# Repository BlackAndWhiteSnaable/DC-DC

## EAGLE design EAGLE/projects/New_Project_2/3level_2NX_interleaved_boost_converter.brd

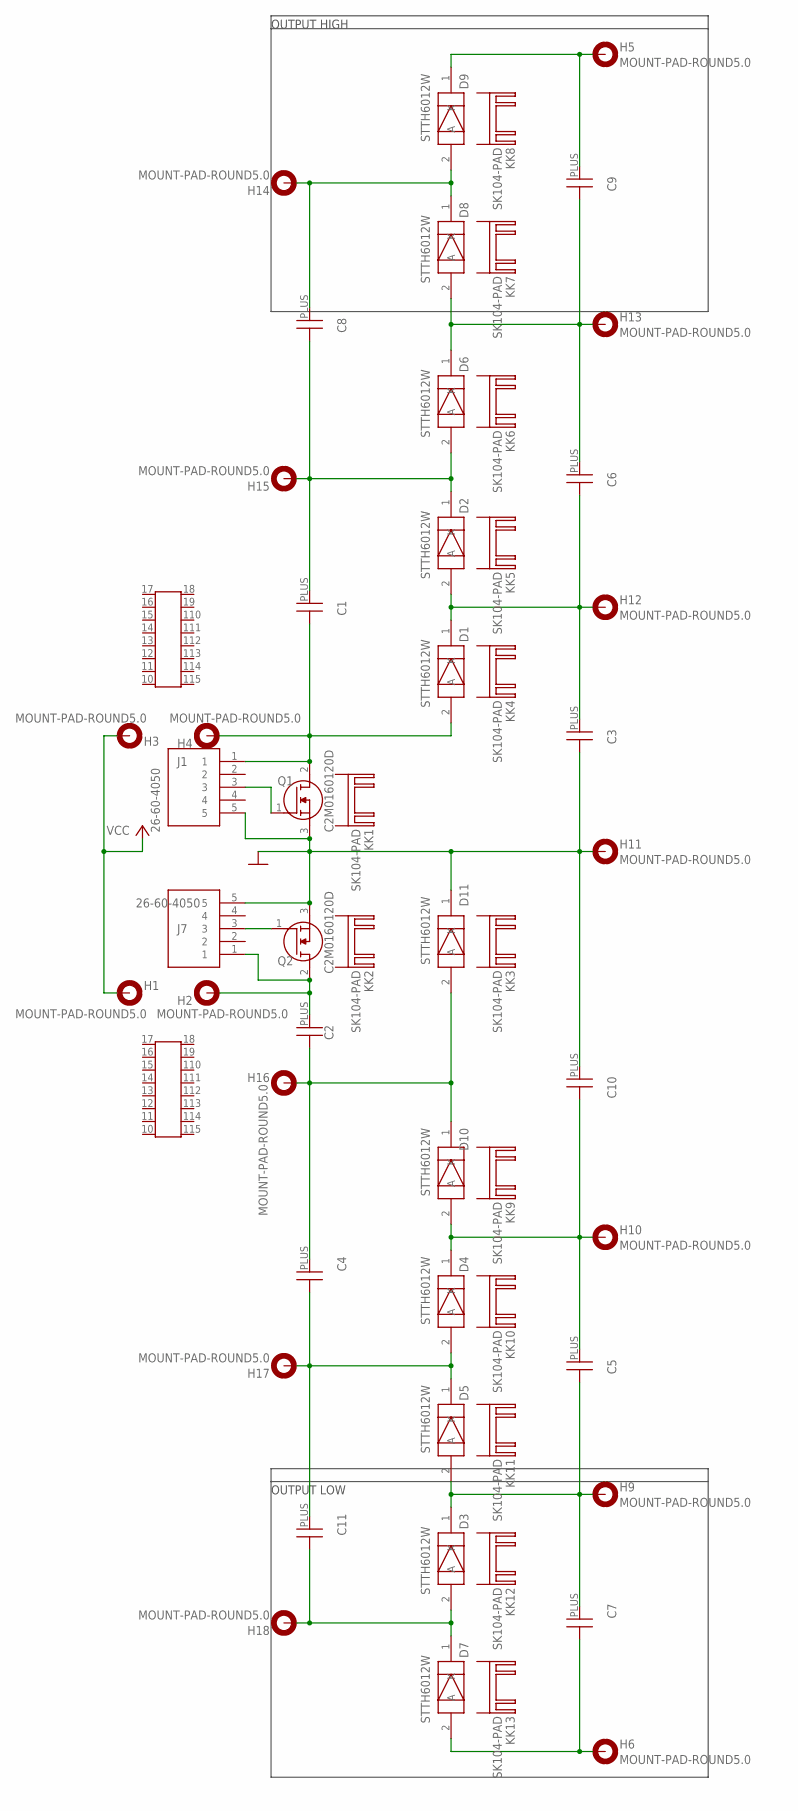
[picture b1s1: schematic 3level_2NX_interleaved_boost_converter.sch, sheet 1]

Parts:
C1, C2, C3, C4, C5, C6, C7, C8, C9, C10, C11: SANJEECAP; ECA2WHG2R2
D1, D2, D3, D4, D5, D6, D7, D8, D9, D10, D11: STTH6012W; TO1090P515X1560X2445-2P
H1, H2, H3, H4, H5, H6, H9, H10, H11, H12, H13, H14, H15, H16, H17, H18: MOUNT-PAD-ROUND5.0; 5,0-PAD
J1, J7: 26-60-4050; SHDR5W155P0X396_1X5_1966X1001X
KK1, KK2, KK3, KK4, KK5, KK6, KK7, KK8, KK9, KK10, KK11, KK12, KK13: SK104-PAD
Q1, Q2: C2M0160120D; TO544P521X1594X2550-3P
U$1, U$2: JELL; BOBBIN

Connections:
GND: C3.MINUS (1), C10.PLUS (2), D11.1 (K), H11.B5, J1.5, J7.5, Q1.3 (S), Q2.3 (S); also elsewhere on the board
unnamed: C1.PLUS (2), C8.MINUS (1), D2.1 (K), D6.2 (A), H15.B5
unnamed: C1.MINUS (1), D1.2 (A), H4.B5, J1.1, Q1.2 (D)
unnamed: C3.PLUS (2), C6.MINUS (1), D1.1 (K), D2.2 (A), H12.B5
unnamed: C8.PLUS (2), D8.1 (K), D9.2 (A), H14.B5
unnamed: C2.PLUS (2), H2.B5, J7.1, Q2.2 (D)
unnamed: C9.PLUS (2), D9.1 (K), H5.B5
unnamed: C11.MINUS (1), D3.2 (A), D7.1 (K), H18.B5
unnamed: C7.MINUS (1), D7.2 (A), H6.B5
unnamed: C2.MINUS (1), C4.PLUS (2), D10.1 (K), D11.2 (A), H16.B5
unnamed: C5.PLUS (2), C10.MINUS (1), D4.1 (K), D10.2 (A), H10.B5
unnamed: C6.PLUS (2), C9.MINUS (1), D6.1 (K), D8.2 (A), H13.B5
unnamed: J1.3, Q1.1 (G)
unnamed: J7.3, Q2.1 (G)
unnamed: C4.MINUS (1), C11.PLUS (2), D4.2 (A), D5.1 (K), H17.B5
unnamed: C5.MINUS (1), C7.PLUS (2), D3.1 (K), D5.2 (A), H9.B5
VCC: H1.B5, H3.B5; also elsewhere on the board

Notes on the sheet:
OUTPUT HIGH
OUTPUT LOW

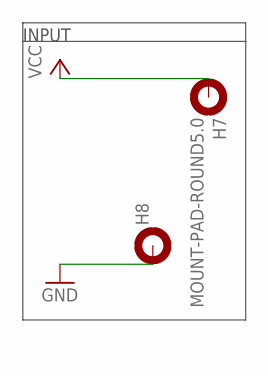
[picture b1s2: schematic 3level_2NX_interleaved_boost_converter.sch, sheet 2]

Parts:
H7, H8: MOUNT-PAD-ROUND5.0; 5,0-PAD

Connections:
GND: H8.B5; also elsewhere on the board
VCC: H7.B5; also elsewhere on the board

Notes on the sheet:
INPUT

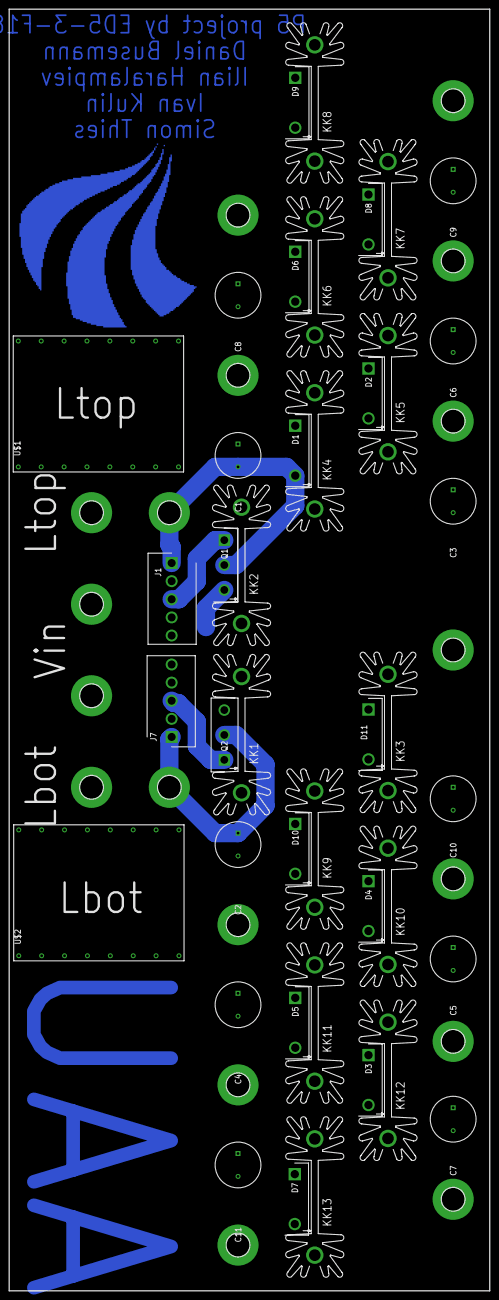
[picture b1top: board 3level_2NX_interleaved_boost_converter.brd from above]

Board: 2 copper layers, 105.0 x 280.0 mm, 59 parts (0 on the bottom side), 17 nets.

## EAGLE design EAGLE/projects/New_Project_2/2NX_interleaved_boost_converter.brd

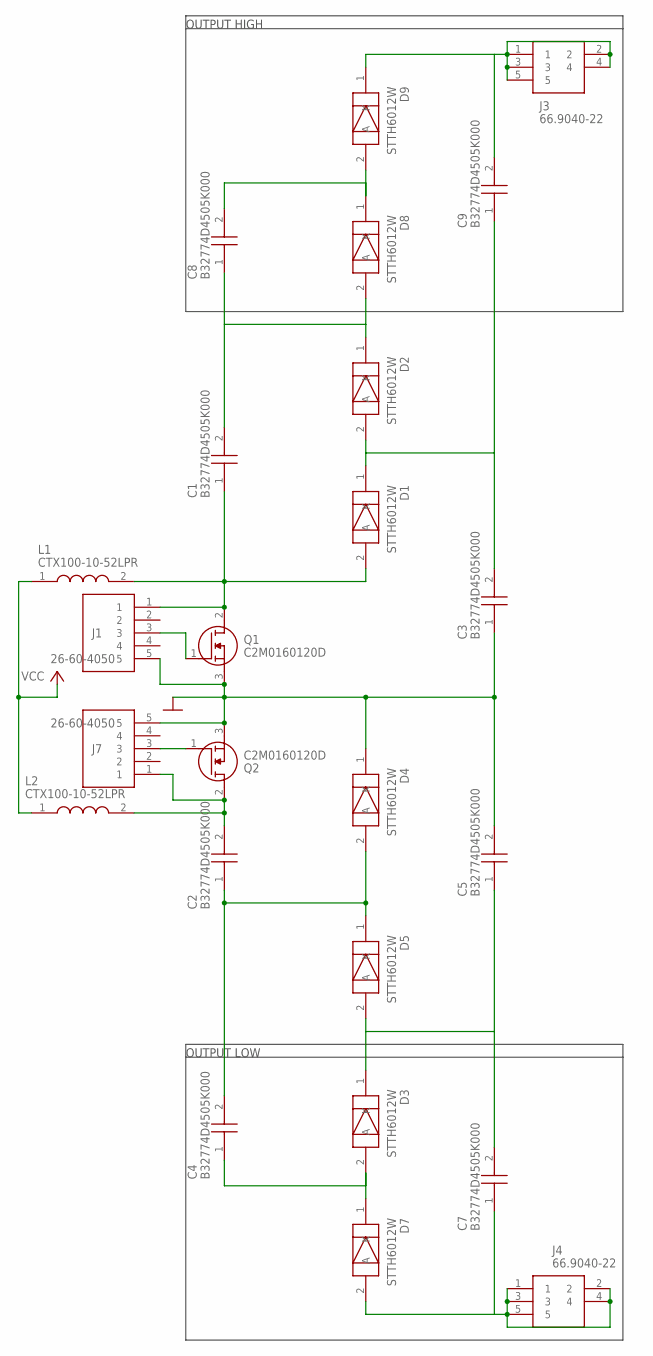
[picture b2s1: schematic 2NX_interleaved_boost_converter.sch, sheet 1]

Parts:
C1, C2, C3, C4, C5, C7, C8, C9: B32774D4505K000
D1, D2, D3, D4, D5, D7, D8, D9: STTH6012W; TO1090P515X1560X2445-2P
J1, J7: 26-60-4050; SHDR5W155P0X396_1X5_1966X1001X
J3, J4: 66.9040-22; 66904022
L1, L2: CTX100-10-52LPR; CTX1001052LPR
Q1, Q2: C2M0160120D; TO544P521X1594X2550-3P

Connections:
GND: C3.1, C5.2, D4.1 (K), J1.5, J7.5, Q1.3 (S), Q2.3 (S); also elsewhere on the board
unnamed: C1.2, C8.1, D2.1 (K), D8.2 (A)
unnamed: C1.1, D1.2 (A), J1.1, L1.2, Q1.2 (D)
unnamed: C3.2, C9.1, D1.1 (K), D2.2 (A)
unnamed: C8.2, D8.1 (K), D9.2 (A)
unnamed: C2.2, J7.1, L2.2, Q2.2 (D)
unnamed: C9.2, D9.1 (K), J3.1, J3.2, J3.3, J3.4, J3.5
unnamed: C4.1, D3.2 (A), D7.1 (K)
unnamed: C2.1, C4.2, D4.2 (A), D5.1 (K)
unnamed: C5.1, C7.2, D3.1 (K), D5.2 (A)
unnamed: C7.1, D7.2 (A), J4.1, J4.2, J4.3, J4.4, J4.5
unnamed: J1.3, Q1.1 (G)
unnamed: J7.3, Q2.1 (G)
VCC: L1.1, L2.1; also elsewhere on the board

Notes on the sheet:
OUTPUT HIGH
OUTPUT LOW

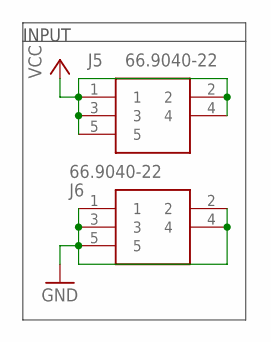
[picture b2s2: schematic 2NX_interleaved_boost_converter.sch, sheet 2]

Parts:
J5, J6: 66.9040-22; 66904022

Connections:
GND: J6.1, J6.2, J6.3, J6.4, J6.5; also elsewhere on the board
VCC: J5.1, J5.2, J5.3, J5.4, J5.5; also elsewhere on the board

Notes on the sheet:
INPUT

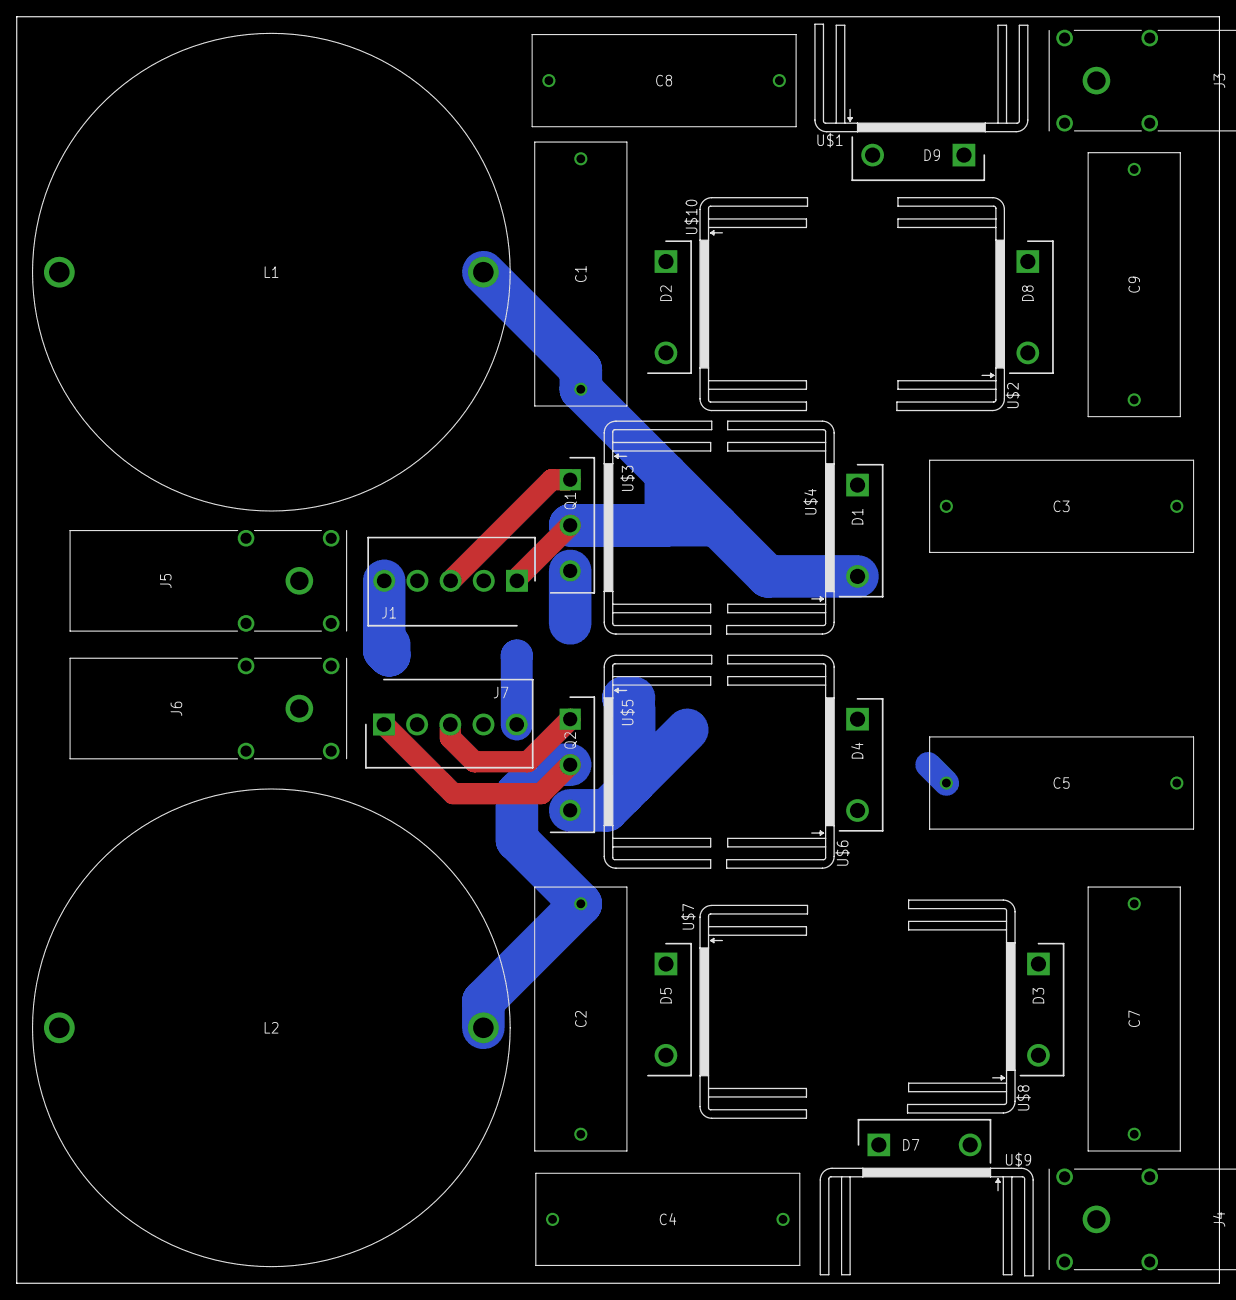
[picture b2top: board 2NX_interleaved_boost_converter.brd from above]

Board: 2 copper layers, 143.5 x 151.1 mm, 36 parts (0 on the bottom side), 14 nets.

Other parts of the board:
U$1, U$2, U$3, U$4, U$5, U$6, U$7, U$8, U$9, U$10: FK213

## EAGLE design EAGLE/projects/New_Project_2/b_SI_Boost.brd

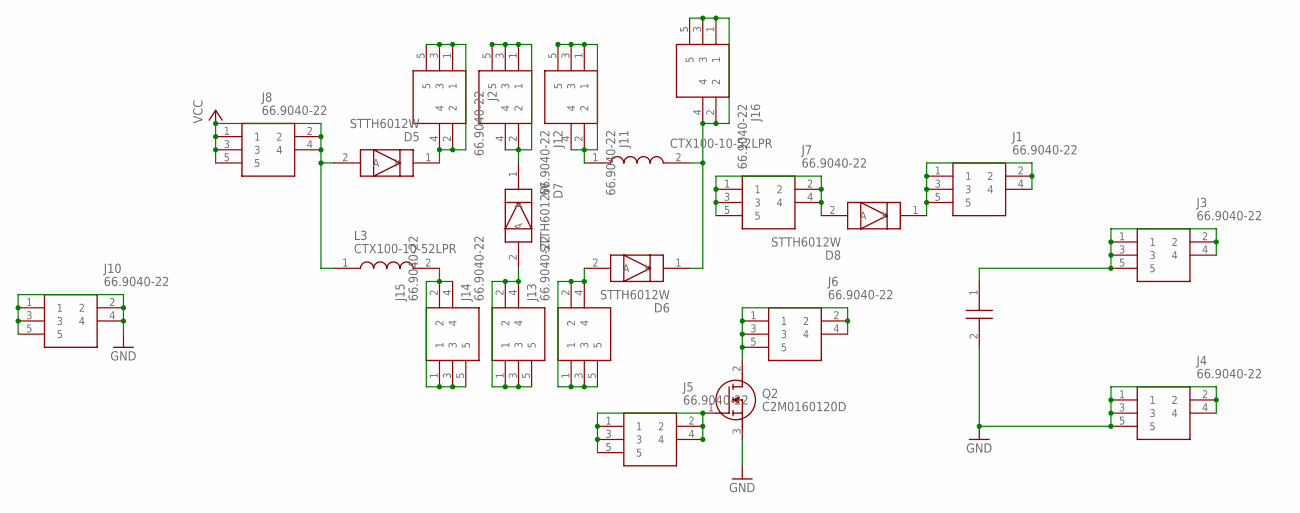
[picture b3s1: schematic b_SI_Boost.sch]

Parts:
D5, D6, D7, D8: STTH6012W; TO1090P515X1560X2445-2P
J1, J2, J3, J4, J5, J6, J7, J8, J10, J11, J12, J13, J14, J15, J16: 66.9040-22; 66904022
L3, L4: CTX100-10-52LPR; CTX1001052LPR
Q2: C2M0160120D; TO544P521X1594X2550-3P
U$1: B32774D4505K000

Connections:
GND: J4.1, J4.2, J4.3, J4.4, J4.5, J10.1, J10.2, J10.3, J10.4, J10.5, Q2.3 (S), U$1.2
unnamed: J15.1, J15.2, J15.3, J15.4, J15.5, L3.2
unnamed: D7.2 (A), J14.1, J14.2, J14.3, J14.4, J14.5
unnamed: D6.1 (K), J16.1, J16.2, J16.3, J16.4, J16.5, L4.2
unnamed: D8.1 (K), J1.1, J1.2, J1.3, J1.4, J1.5
unnamed: J3.1, J3.2, J3.3, J3.4, J3.5, U$1.1
unnamed: J6.1, J6.2, J6.3, J6.4, J6.5, Q2.2 (D)
unnamed: D8.2 (A), J7.1, J7.2, J7.3, J7.4, J7.5
unnamed: J5.1, J5.2, J5.3, J5.4, J5.5, Q2.1 (G)
unnamed: D6.2 (A), J13.1, J13.2, J13.3, J13.4, J13.5
unnamed: D7.1 (K), J12.1, J12.2, J12.3, J12.4, J12.5
unnamed: D5.1 (K), J2.1, J2.2, J2.3, J2.4, J2.5
unnamed: J11.1, J11.2, J11.3, J11.4, J11.5, L4.1
VCC: D5.2 (A), J8.1, J8.2, J8.3, J8.4, J8.5, L3.1

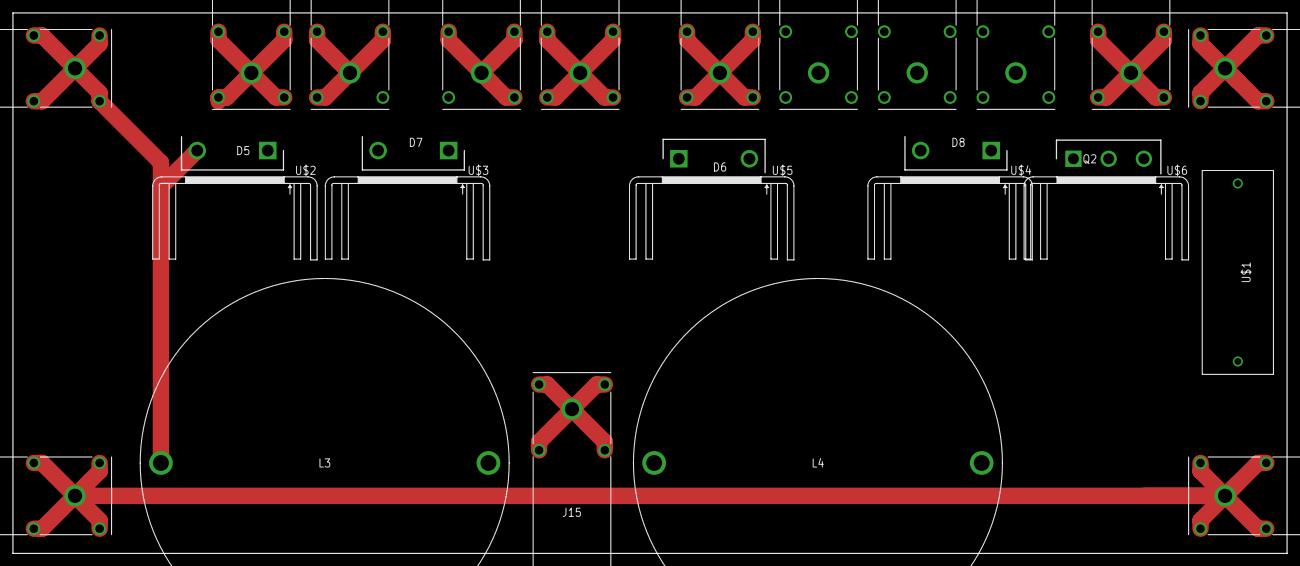
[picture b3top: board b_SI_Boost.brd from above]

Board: 2 copper layers, 196.8 x 83.5 mm, 27 parts (0 on the bottom side), 13 nets.

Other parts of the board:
U$2, U$3, U$4, U$5, U$6: FK213

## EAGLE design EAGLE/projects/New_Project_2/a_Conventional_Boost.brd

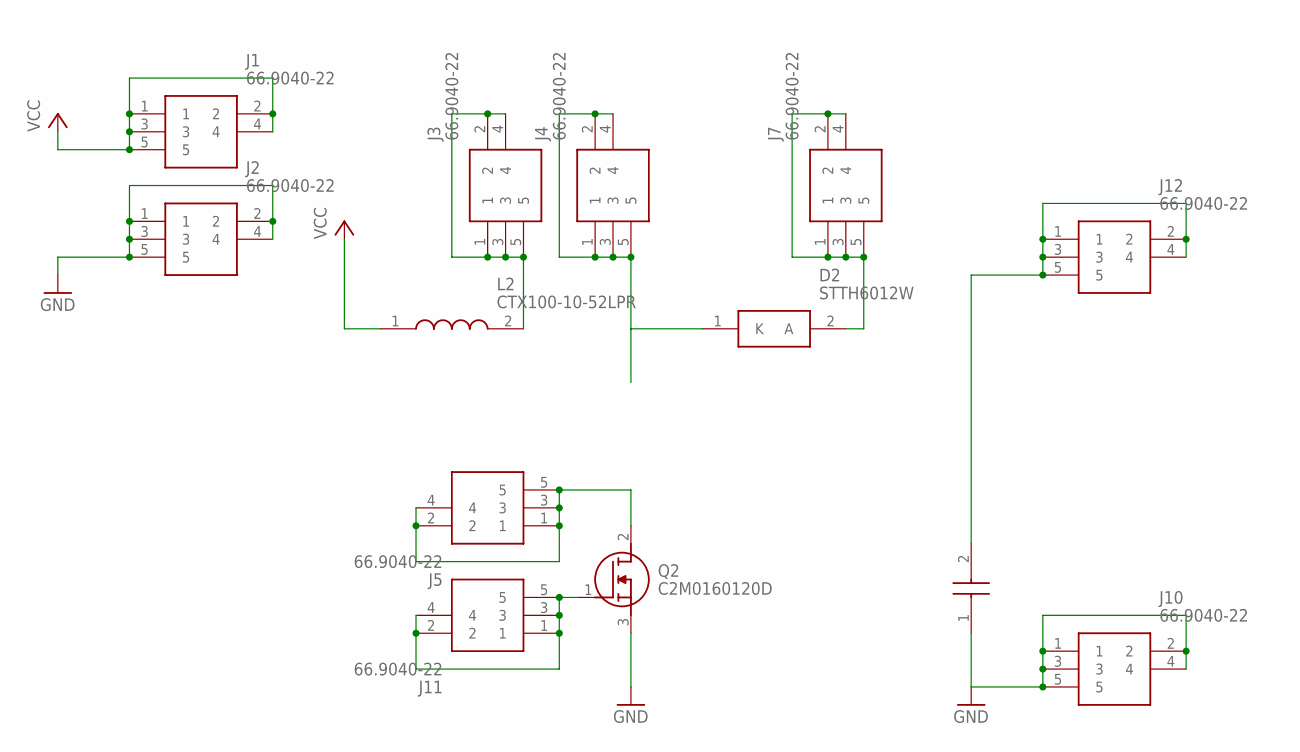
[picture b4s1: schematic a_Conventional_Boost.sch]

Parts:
D2: STTH6012W; TO1090P515X1560X2445-2P
J1, J2, J3, J4, J5, J7, J10, J11, J12: 66.9040-22; 66904022
L2: CTX100-10-52LPR; CTX1001052LPR
Q2: C2M0160120D; TO544P521X1594X2550-3P
U$1: B32774D4505K000

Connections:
GND: J2.1, J2.2, J2.3, J2.4, J2.5, J10.1, J10.2, J10.3, J10.4, J10.5, Q2.3 (S), U$1.1
GND1: J11.1, J11.2, J11.3, J11.4, J11.5, Q2.1 (G)
unnamed: D2.1 (K), J4.1, J4.2, J4.3, J4.4, J4.5
VCC: J1.1, J1.2, J1.3, J1.4, J1.5, L2.1
VCC1: J3.1, J3.2, J3.3, J3.4, J3.5, L2.2
VCC2: J5.1, J5.2, J5.3, J5.4, J5.5, Q2.2 (D)
VCC3: D2.2 (A), J7.1, J7.2, J7.3, J7.4, J7.5
VCC4: J12.1, J12.2, J12.3, J12.4, J12.5, U$1.2

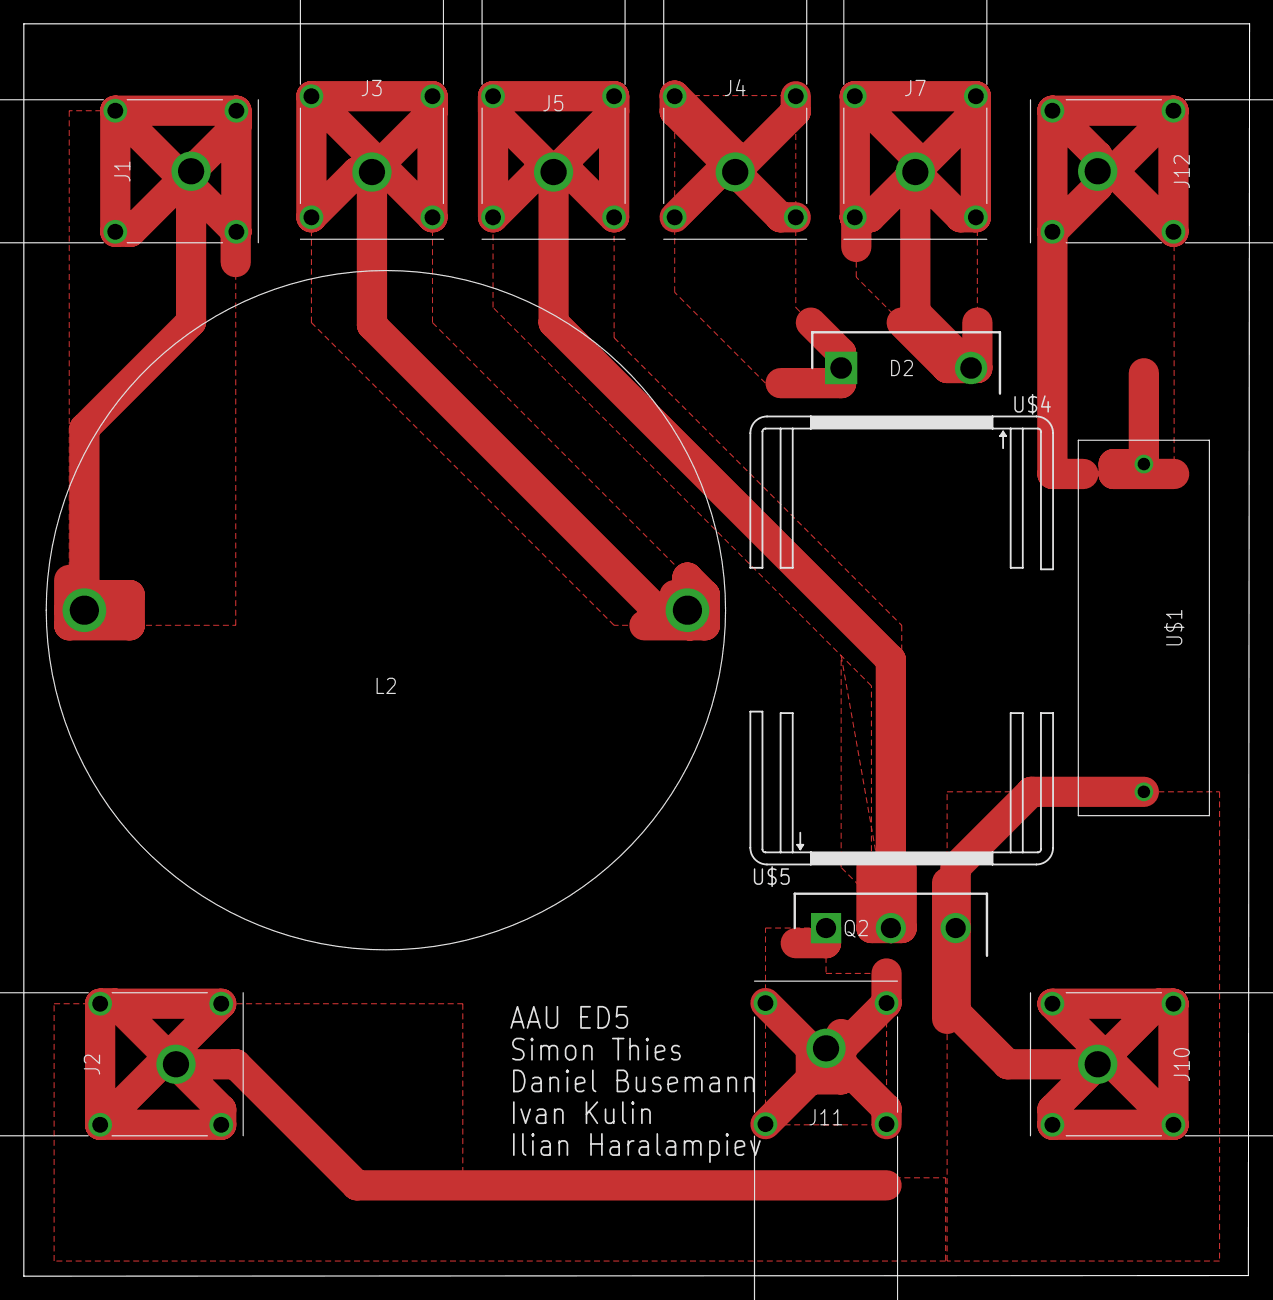
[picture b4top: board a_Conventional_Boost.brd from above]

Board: 2 copper layers, 102.8 x 105.1 mm, 15 parts (0 on the bottom side), 8 nets.

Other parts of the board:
U$4, U$5: FK213

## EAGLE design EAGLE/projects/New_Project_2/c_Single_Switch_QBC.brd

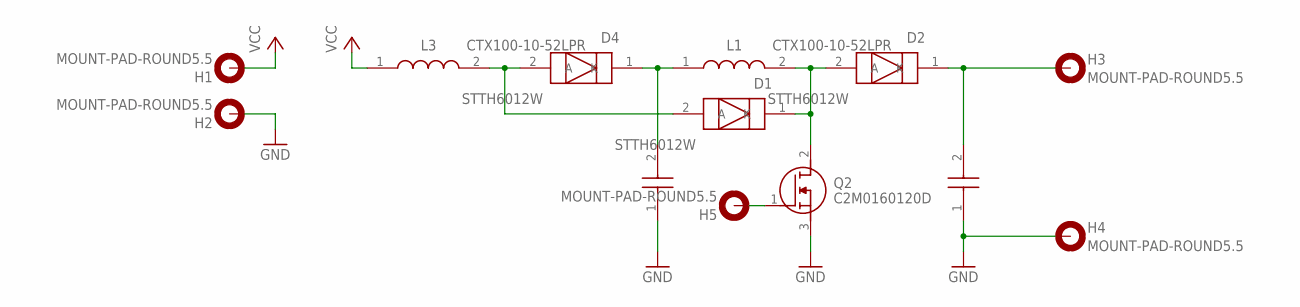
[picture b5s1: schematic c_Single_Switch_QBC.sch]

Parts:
D1, D2, D4: STTH6012W; TO1090P515X1560X2445-2P
H1, H2, H3, H4, H5: MOUNT-PAD-ROUND5.5; 5,5-PAD
L1, L3: CTX100-10-52LPR; CTX1001052LPR
Q2: C2M0160120D; TO544P521X1594X2550-3P
U$1, U$2: B32774D4505K000

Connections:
GND: H2.B5,5, H4.B5,5, Q2.3 (S), U$1.1, U$2.1
unnamed: D1.2 (A), D4.2 (A), L3.2
unnamed: D2.1 (K), H3.B5,5, U$2.2
unnamed: D1.1 (K), D2.2 (A), L1.2, Q2.2 (D)
unnamed: H5.B5,5, Q2.1 (G)
unnamed: D4.1 (K), L1.1, U$1.2
VCC: H1.B5,5, L3.1

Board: 2 copper layers, 13 parts (0 on the bottom side), 7 nets, no tracks yet.

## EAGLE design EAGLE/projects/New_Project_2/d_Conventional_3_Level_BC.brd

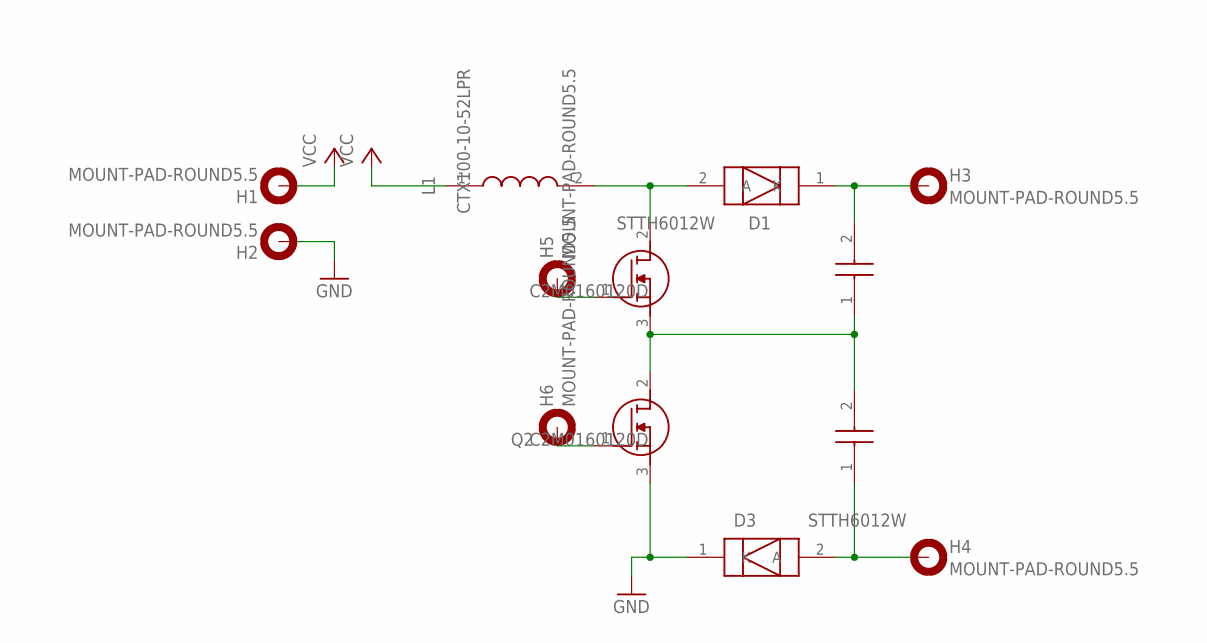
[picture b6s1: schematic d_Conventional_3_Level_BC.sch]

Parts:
D1, D3: STTH6012W; TO1090P515X1560X2445-2P
H1, H2, H3, H4, H5, H6: MOUNT-PAD-ROUND5.5; 5,5-PAD
L1: CTX100-10-52LPR; CTX1001052LPR
Q1, Q2: C2M0160120D; TO544P521X1594X2550-3P
U$3, U$4: B32774D4505K000

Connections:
GND: D3.1 (K), H2.B5,5, Q2.3 (S)
unnamed: Q1.3 (S), Q2.2 (D), U$3.1, U$4.2
unnamed: H5.B5,5, Q1.1 (G)
unnamed: D1.2 (A), L1.2, Q1.2 (D)
unnamed: D1.1 (K), H3.B5,5, U$3.2
unnamed: H6.B5,5, Q2.1 (G)
unnamed: D3.2 (A), H4.B5,5, U$4.1
VCC: H1.B5,5, L1.1

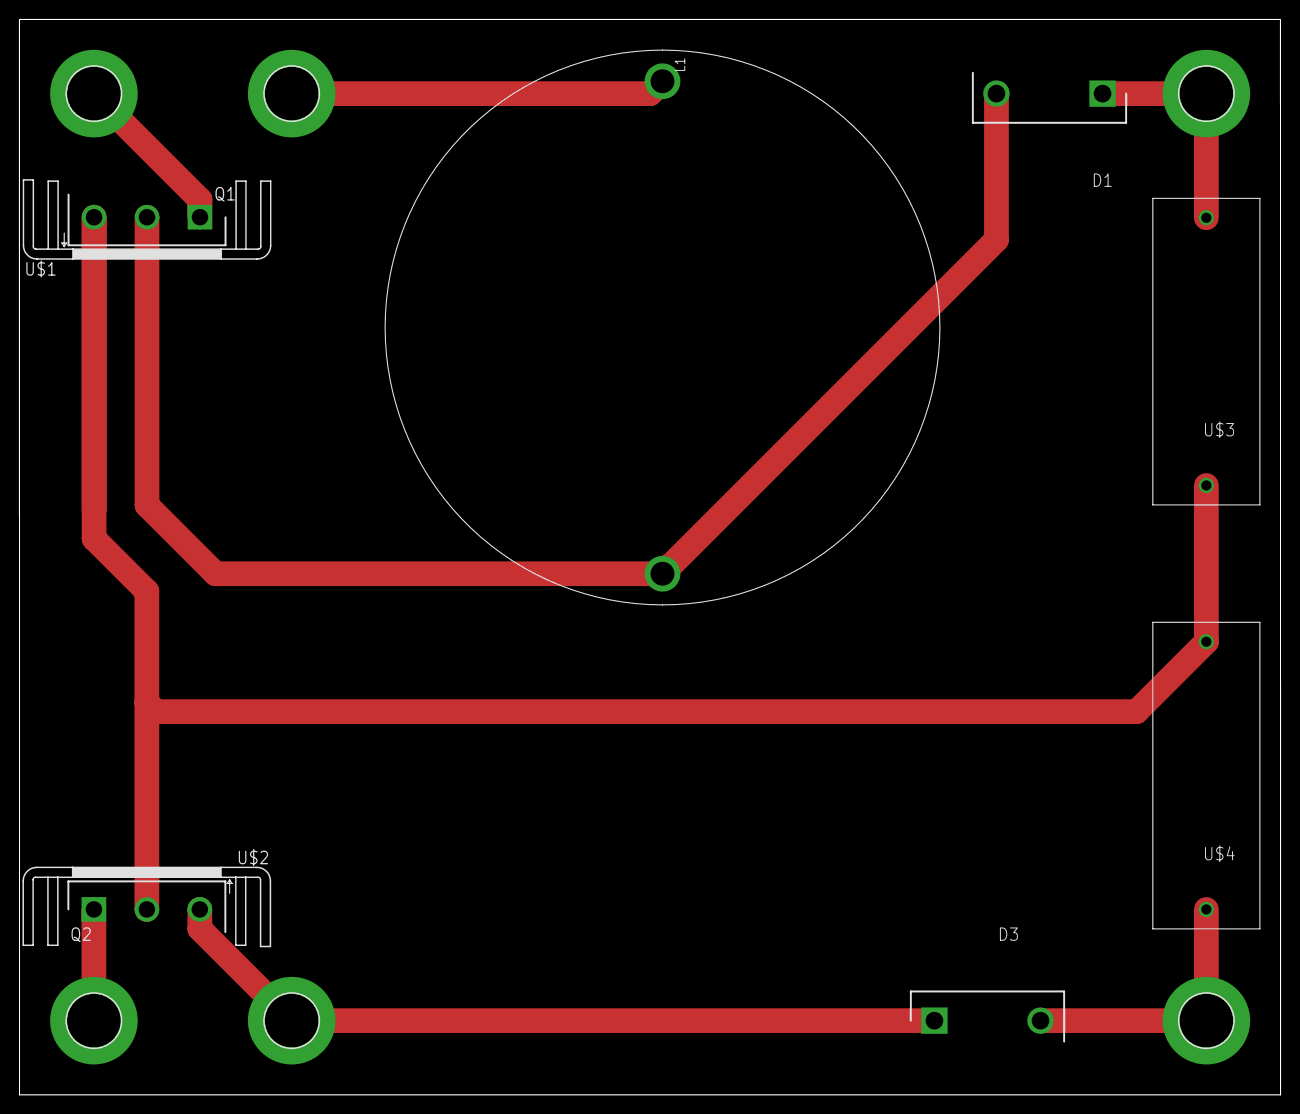
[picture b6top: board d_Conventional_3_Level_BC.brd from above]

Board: 2 copper layers, 129.6 x 110.5 mm, 15 parts (0 on the bottom side), 8 nets.

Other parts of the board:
U$1, U$2: FK209

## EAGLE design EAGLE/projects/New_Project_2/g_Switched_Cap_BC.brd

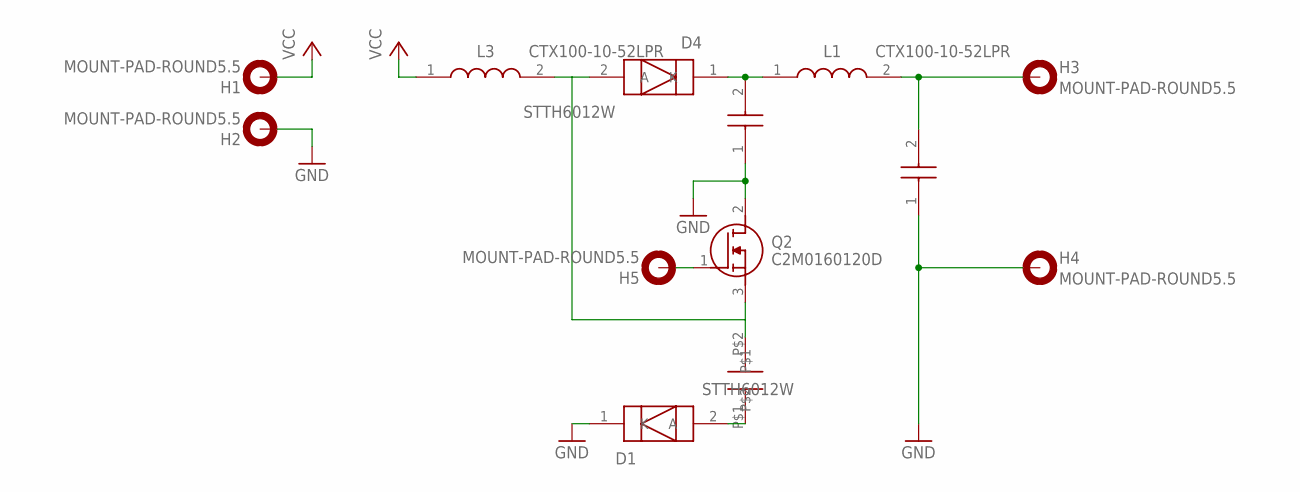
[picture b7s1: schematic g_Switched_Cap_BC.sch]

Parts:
C1, C3: B32774D4505K000
C2: PH_B32774D4505K000PLACEHOLDER; TJ4-U1
D1, D4: STTH6012W; TO1090P515X1560X2445-2P
H1, H2, H3, H4, H5: MOUNT-PAD-ROUND5.5; 5,5-PAD
L1, L3: CTX100-10-52LPR; CTX1001052LPR
Q2: C2M0160120D; TO544P521X1594X2550-3P

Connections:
GND: C1.1, C3.1, D1.1 (K), H2.B5,5, H4.B5,5, Q2.2 (D)
unnamed: C2.P$2, D4.2 (A), L3.2, Q2.3 (S)
unnamed: C2.P$1, D1.2 (A)
unnamed: H5.B5,5, Q2.1 (G)
unnamed: C3.2, H3.B5,5, L1.2
unnamed: C1.2, D4.1 (K), L1.1
VCC: H1.B5,5, L3.1

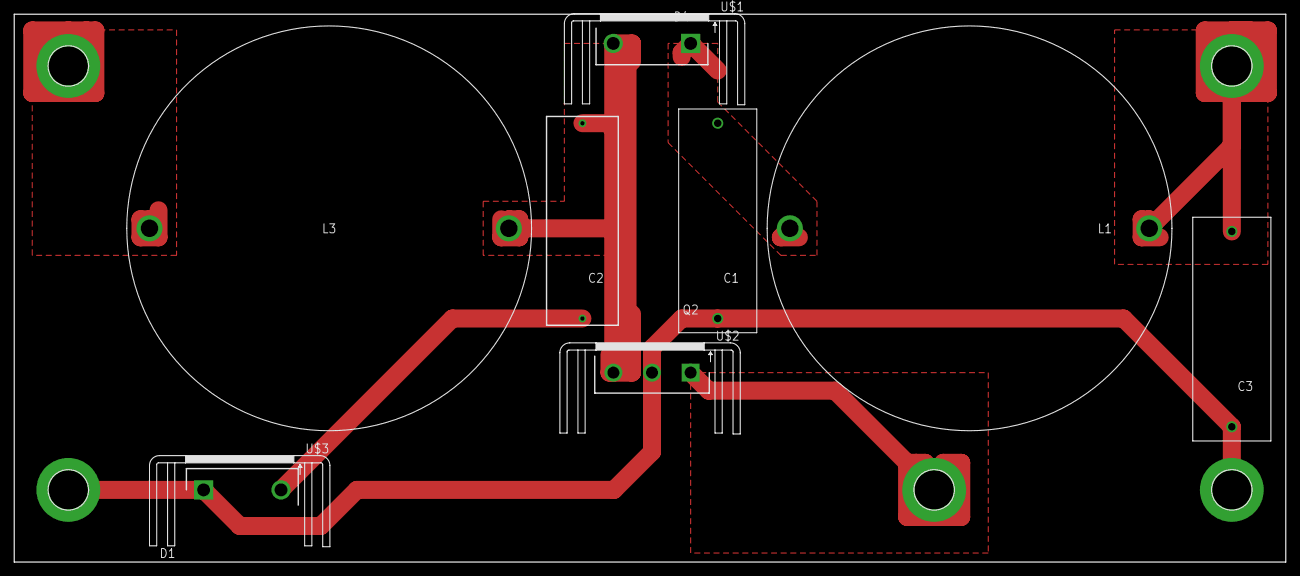
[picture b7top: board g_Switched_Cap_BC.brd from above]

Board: 2 copper layers, 179.1 x 77.1 mm, 16 parts (0 on the bottom side), 7 nets.

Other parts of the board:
U$1, U$2, U$3: FK213

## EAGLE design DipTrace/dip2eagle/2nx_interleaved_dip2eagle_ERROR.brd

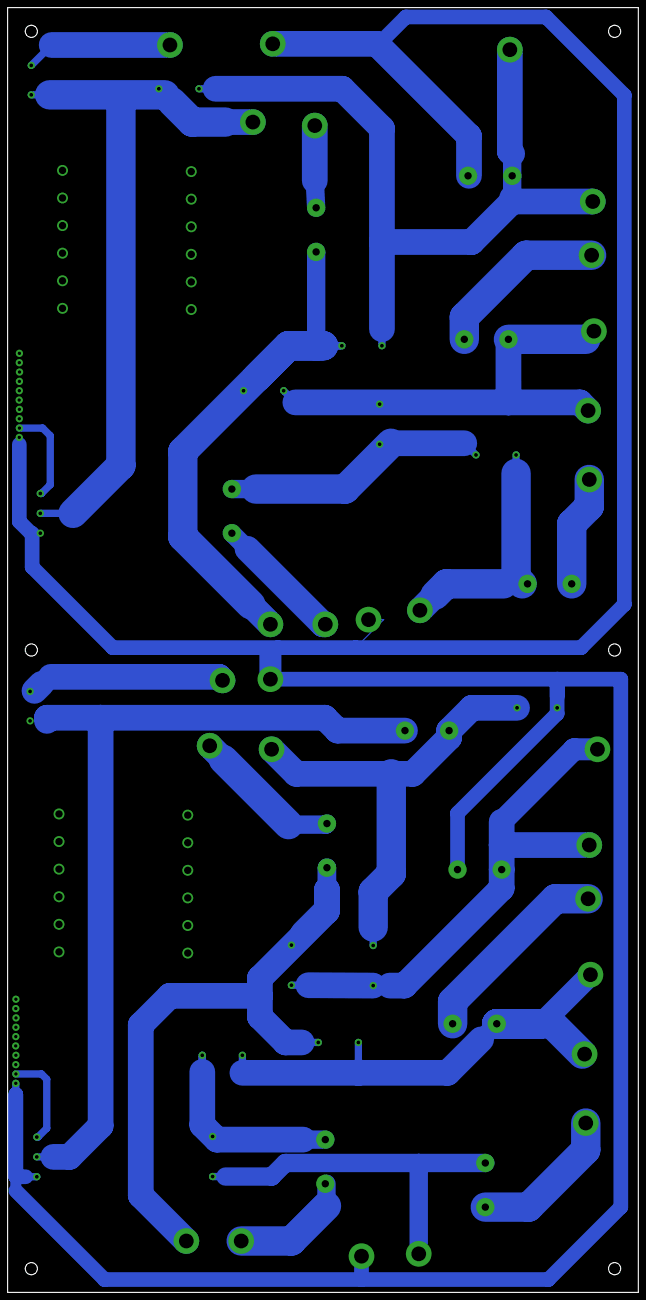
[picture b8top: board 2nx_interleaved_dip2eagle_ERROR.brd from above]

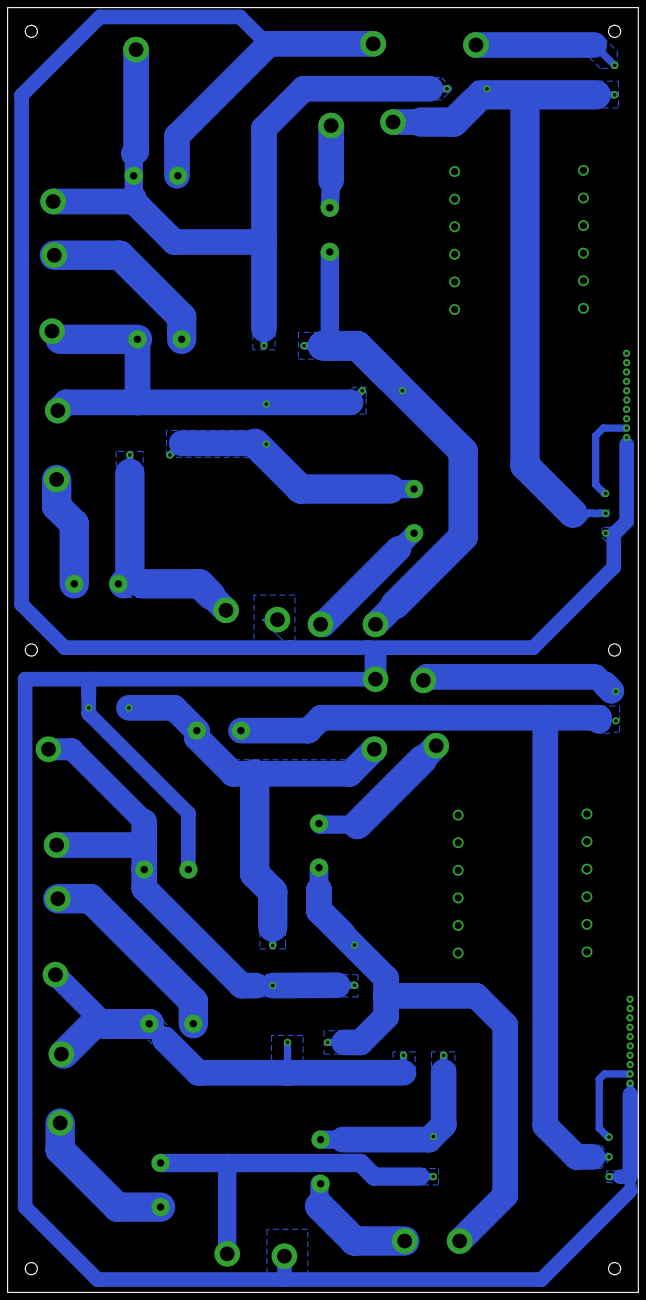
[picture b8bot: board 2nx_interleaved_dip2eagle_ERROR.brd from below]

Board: 2 copper layers, 171.4 x 349.2 mm, 120 parts (94 on the bottom side), 26 nets.

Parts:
PAD1, PAD2, PAD3, PAD4, PAD5, PAD6, PAD7, PAD8, PAD9, PAD10, PAD11, PAD12, PAD13, PAD14, PAD15, PAD16, PAD17, PAD18, PAD19, PAD20, PAD21, PAD22: PAD1
Pad1, Pad24, Pad25, Pad26, Pad27, Pad28, Pad30, Pad31, Pad32, Pad33, Pad34, Pad35, Pad36, Pad45, Pad47, Pad48, Pad71, Pad72, Pad73, Pad74, Pad75, Pad76, Pad77, Pad78, Pad79, Pad80, Pad81, Pad82: Pad
Pad2, Pad3, Pad4, Pad5, Pad6, Pad7, Pad8, Pad9, Pad10, Pad11, Pad12, Pad13, Pad49, Pad50, Pad51, Pad52, Pad53, Pad54, Pad55, Pad56, Pad57, Pad58, Pad59, Pad60: Pad_Pad2
Pad14, Pad15, Pad16, Pad17, Pad18, Pad19, Pad20, Pad21, Pad22, Pad23, Pad61, Pad62, Pad63, Pad64, Pad65, Pad66, Pad67, Pad68, Pad69, Pad70, Pad93, Pad94: Pad_Pad14
Pad29, Pad37, Pad38, Pad39, Pad40, Pad41, Pad42, Pad43, Pad44, Pad46, Pad83, Pad84, Pad85, Pad86, Pad87, Pad88, Pad89, Pad90, Pad91, Pad92: Pad_Pad29
U1: P116
U2: P117
U3: P118
U4: P119

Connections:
Net_0: PAD4.1, Pad45.1
Net_1: PAD3.1, Pad36.1, U1.1, U3.1_1
Net_2: PAD2.1, PAD9.1, Pad14.1, Pad32.1
Net_3: PAD1.1, Pad22.1, Pad24.1, Pad25.1, U3.1
Net_4: PAD21.1, Pad1.1, Pad23.1, Pad27.1, Pad29.1, Pad48.1, Pad70.1, Pad82.1, Pad91.1, U1.1_1, U2.1_1
Net_5: PAD5.1, PAD10.1, Pad20.1, Pad28.1, Pad30.1
Net_6: Pad62.1, Pad81.1
Net_7: PAD8.1, Pad18.1, Pad34.1
Net_8: Pad17.1, Pad33.1
Net_9: Pad21.1, Pad26.1
Net_10: Pad19.1, Pad31.1
Net_11: Pad15.1, Pad35.1
Net_12: Pad46.1, U1.1_1
Net_13: PAD16.1, Pad47.1
Net_14: PAD13.1, Pad94.1, U2.1
Net_15: PAD15.1, PAD19.1, Pad61.1, Pad77.1
Net_16: PAD14.1, Pad69.1, Pad71.1, Pad72.1, U4.1
Net_17: PAD6.1, PAD7.1, Pad16.1
Net_18: PAD11.1, PAD20.1, Pad67.1, Pad74.1, Pad75.1
Net_19: PAD12.1, PAD17.1, Pad63.1
Net_20: PAD18.1, Pad65.1, Pad79.1
Net_21: Pad64.1, Pad78.1
Net_22: Pad68.1, Pad73.1
Net_23: Pad66.1, Pad76.1
Net_24: PAD22.1, Pad80.1, Pad93.1, U4.1_1
Net_25: Pad92.1, U2.1_1
